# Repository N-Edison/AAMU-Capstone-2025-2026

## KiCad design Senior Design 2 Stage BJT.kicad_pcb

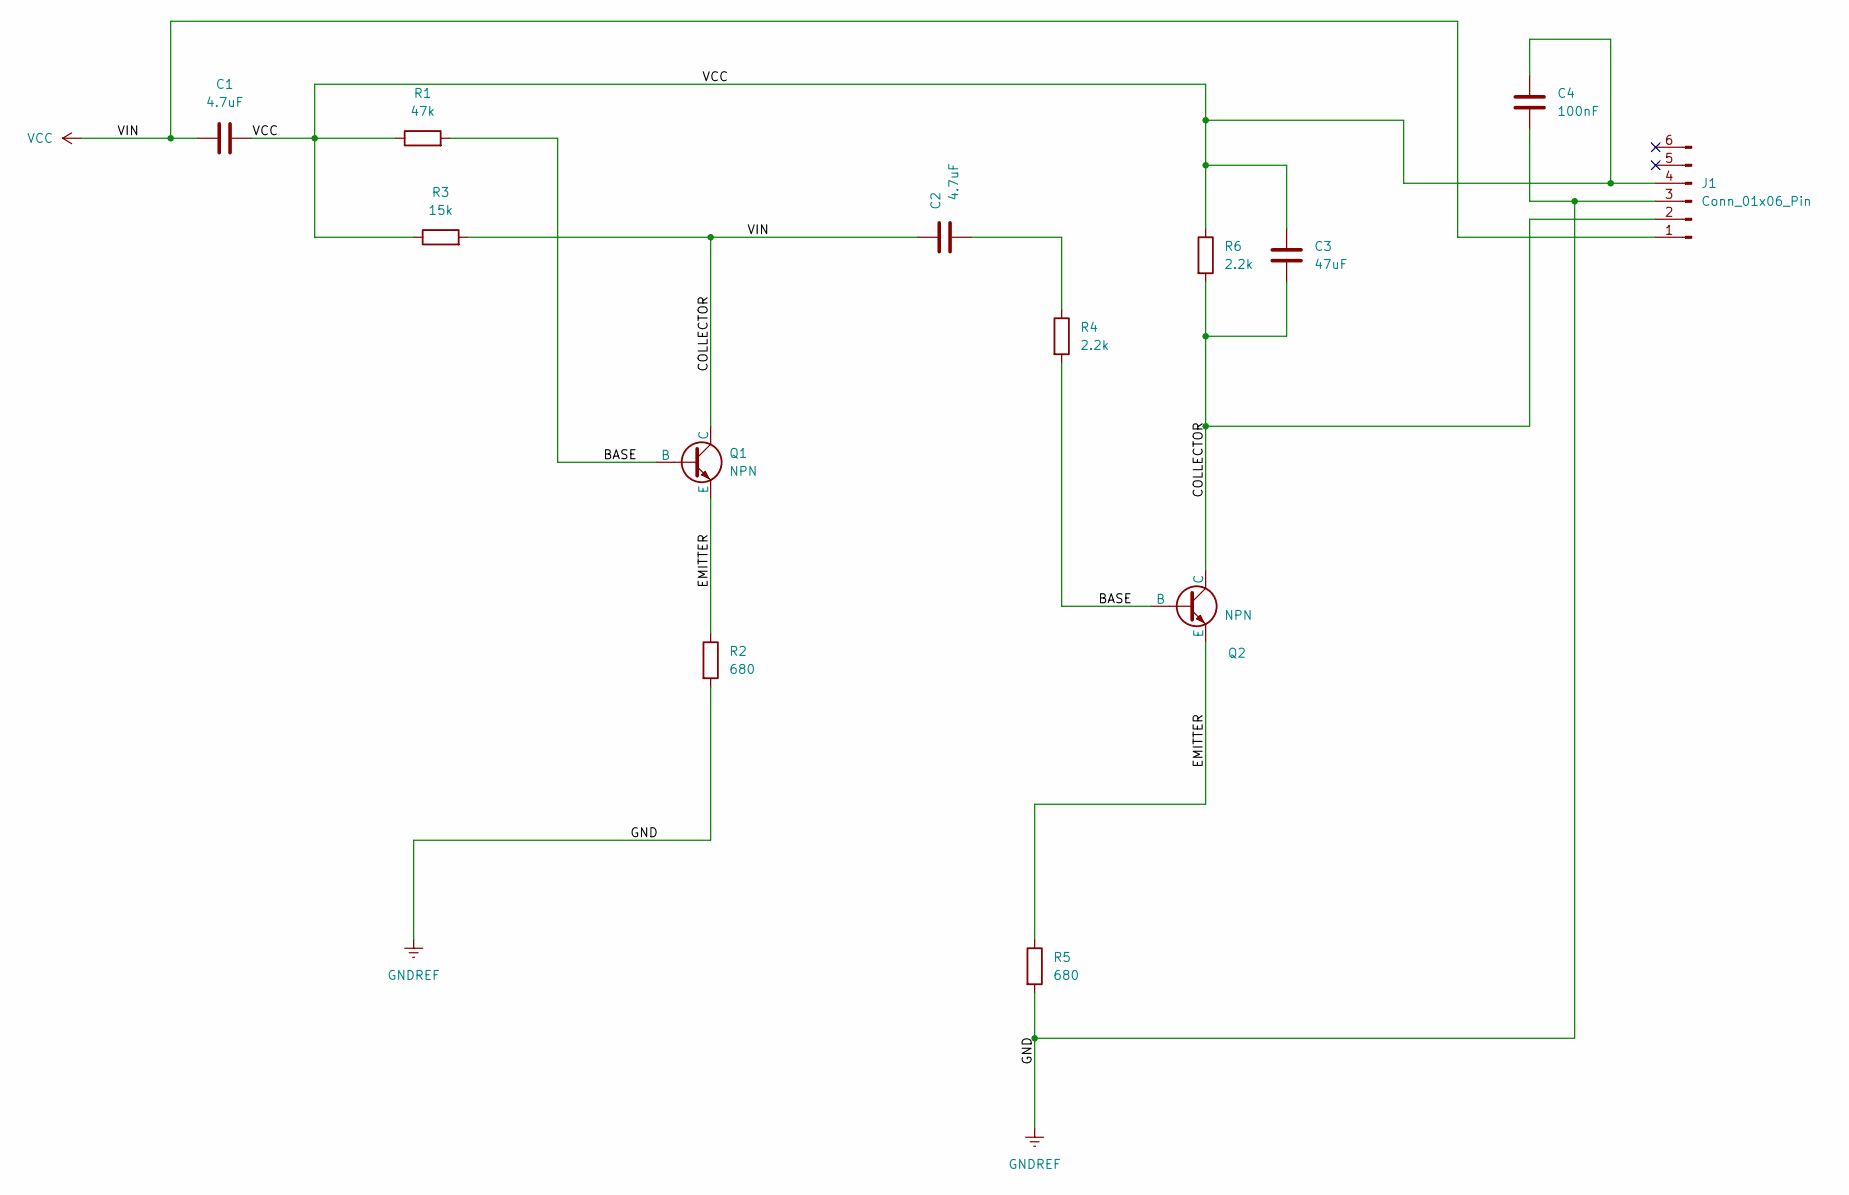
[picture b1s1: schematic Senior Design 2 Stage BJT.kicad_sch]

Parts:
C1, C2: 4.7uF; C_Disc_D5.0mm_W2.5mm_P5.00mm
C3: 47uF; C_Radial_D5.0mm_H5.0mm_P2.00mm
C4: 100nF; C_Disc_D5.0mm_W2.5mm_P5.00mm
J1: Conn_01x06_Pin; Harwin_M20-89006xx_1x06_P2.54mm_Horizontal
Q1, Q2: NPN; TO-92_Inline
R1: 47k; R_Axial_DIN0207_L6.3mm_D2.5mm_P7.62mm_Horizontal
R2, R5: 680; R_Axial_DIN0207_L6.3mm_D2.5mm_P7.62mm_Horizontal
R3: 15k; R_Axial_DIN0207_L6.3mm_D2.5mm_P7.62mm_Horizontal
R4, R6: 2.2k; R_Axial_DIN0207_L6.3mm_D2.5mm_P7.62mm_Horizontal

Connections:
/BASE: Q1.2 (B), Q2.2 (B), R1.2, R4.2
/EMITTER: Q1.3 (E), Q2.3 (E), R2.1, R5.1
GNDREF: C4.2, J1.3, R2.2, R5.2
unnamed: C2.2, R4.1
VCC: C1.1, C1.2, C2.1, C3.1, C3.2, C4.1, J1.1, J1.2, J1.4, Q1.1 (C), Q2.1 (C), R1.1, R3.1, R3.2, R6.1, R6.2

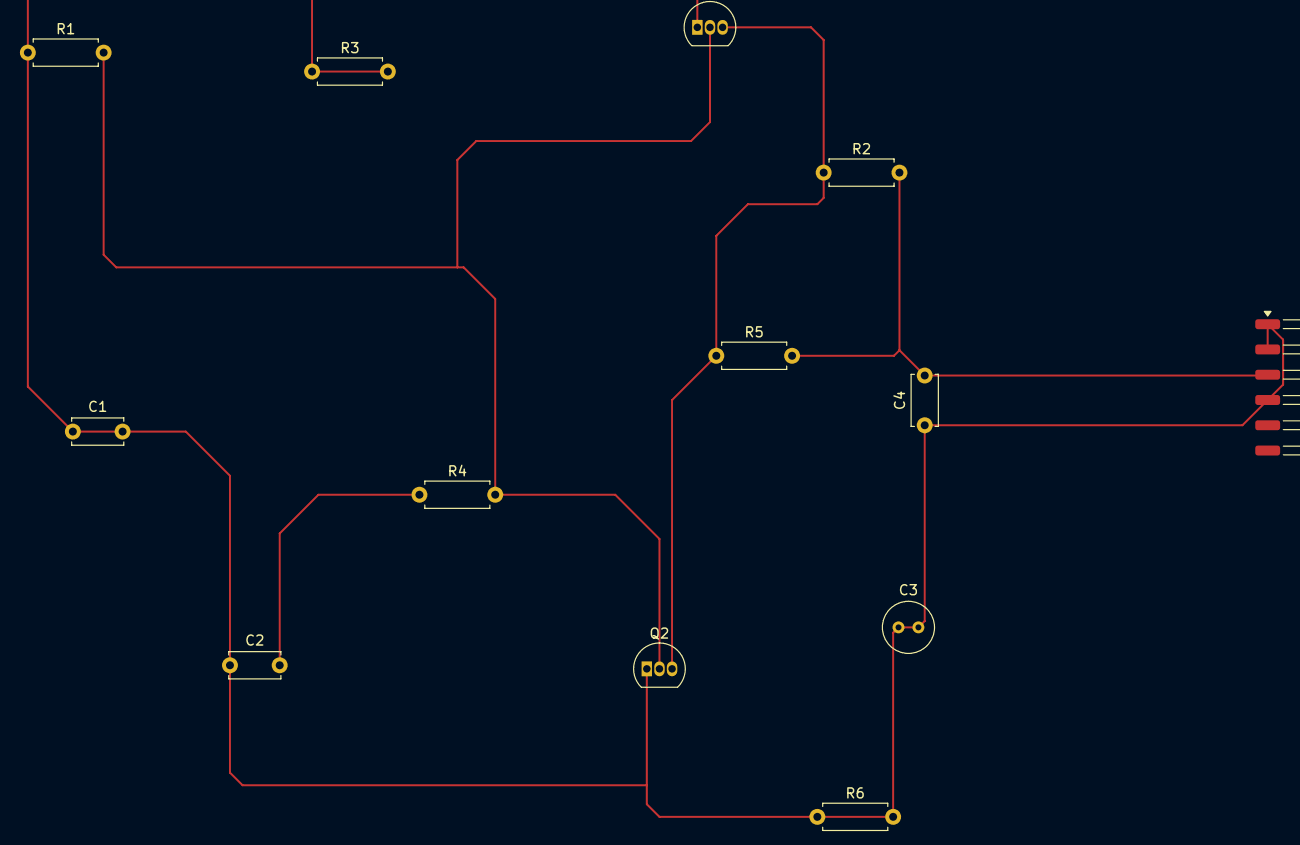
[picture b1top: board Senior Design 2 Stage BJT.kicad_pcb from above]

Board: 2 copper layers, 13 parts (0 on the bottom side), 5 nets.

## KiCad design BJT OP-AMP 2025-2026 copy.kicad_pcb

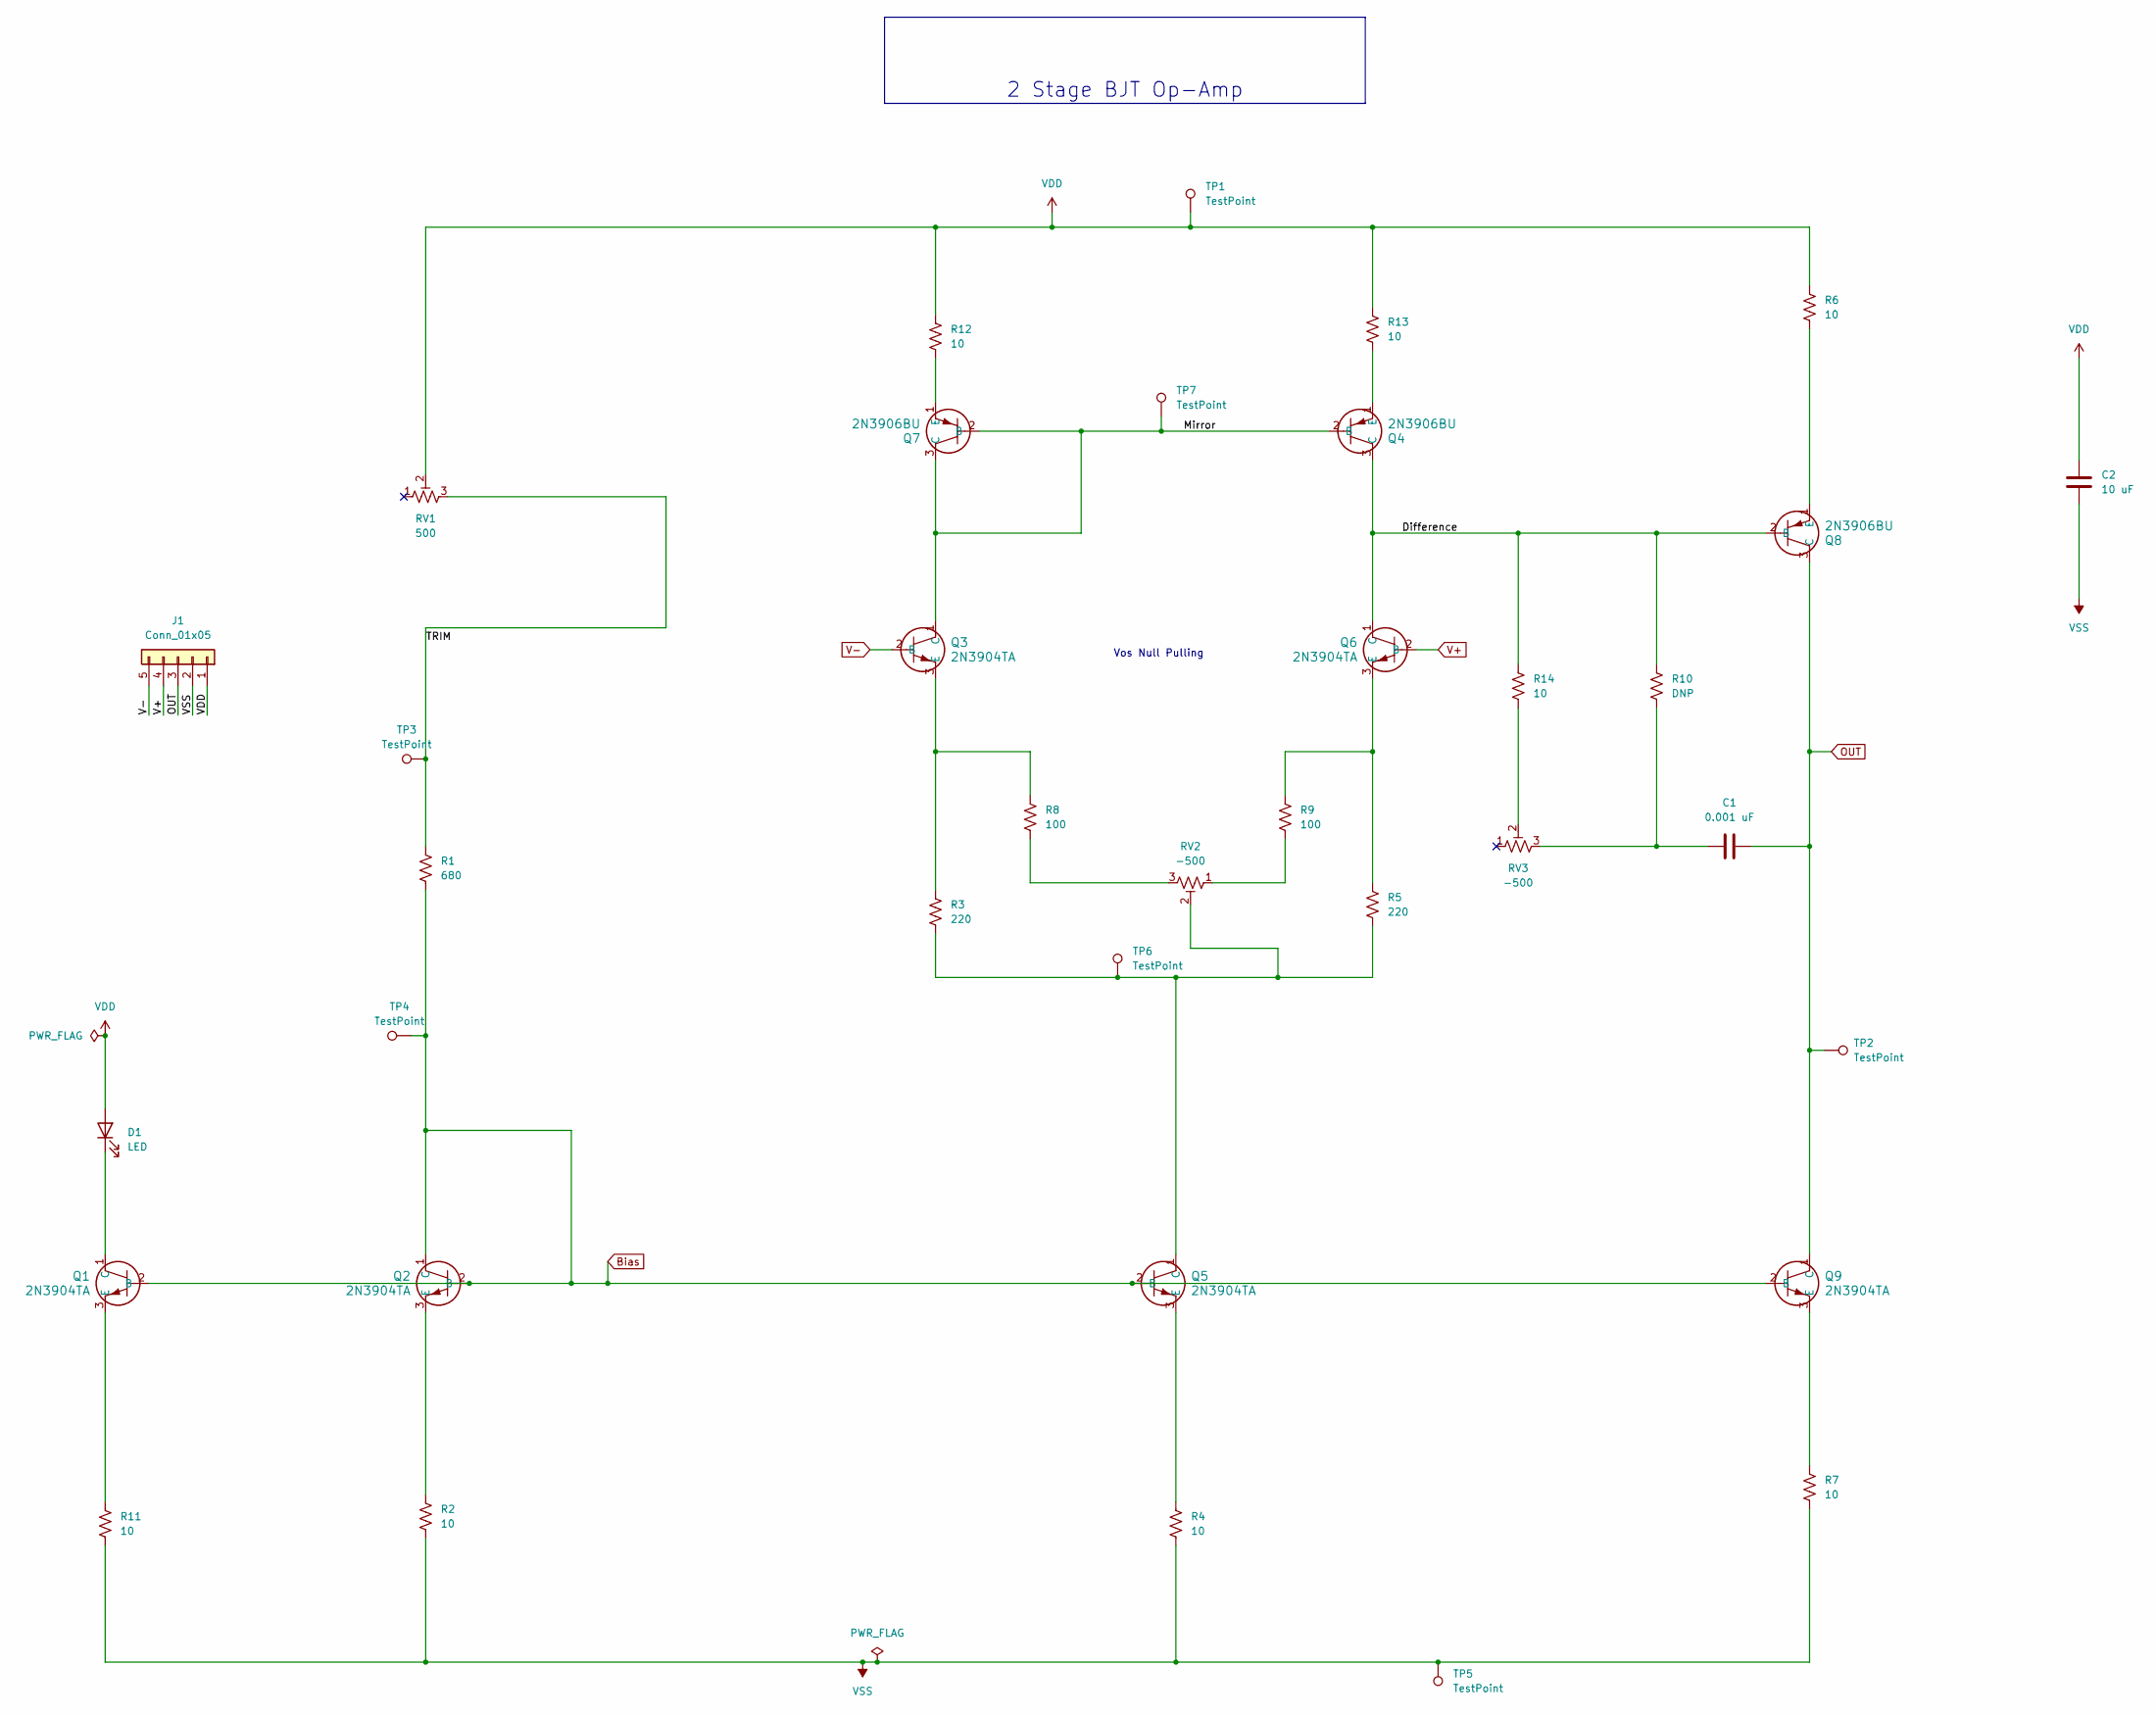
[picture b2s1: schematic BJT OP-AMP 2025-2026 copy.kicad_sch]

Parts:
C1: 0.001 uF; C_0603_1608Metric_Pad1.08x0.95mm_HandSolder
C2: 10 uF; C_0603_1608Metric_Pad1.08x0.95mm_HandSolder
D1: LED; LED_0603_1608Metric_Pad1.05x0.95mm_HandSolder
J1: Conn_01x05; PinHeader_1x05_P2.54mm_Horizontal
Q1, Q2, Q3, Q5, Q6, Q9: 2N3904TA; 2N3904TA_ONS
Q4, Q7, Q8: 2N3906BU; 2N3906BU_ONS
R1: 680; R_0603_1608Metric_Pad0.98x0.95mm_HandSolder
R2, R4, R6, R7, R11, R12, R13, R14: 10; R_0603_1608Metric_Pad0.98x0.95mm_HandSolder
R3, R5: 220; R_0603_1608Metric_Pad0.98x0.95mm_HandSolder
R8, R9: 100; R_0603_1608Metric_Pad0.98x0.95mm_HandSolder
R10: DNP; R_0603_1608Metric_Pad0.98x0.95mm_HandSolder
RV1: 500; TRIM_3306F-1-253
RV2, RV3: -500; TRIM_3306F-1-253
TP1, TP2, TP3, TP4, TP5, TP6, TP7: TestPoint; TestPoint_Pad_D2.0mm

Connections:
/Difference: Q4.3 (C), Q6.1 (C), Q8.2 (B), R10.1, R14.1
/Mirror: Q3.1 (C), Q4.2 (B), Q7.2 (B), Q7.3 (C), TP7.1
/TRIM: R1.1, RV1.3, TP3.1
Bias: Q1.2 (B), Q2.1 (C), Q2.2 (B), Q5.2 (B), Q9.2 (B), R1.2, TP4.1
unnamed: C1.1, R10.2, RV3.3
unnamed: D1.1 (K), Q1.1 (C)
unnamed: Q1.3 (E), R11.1
unnamed: Q2.3 (E), R2.1
unnamed: Q3.3 (E), R3.1, R8.1
unnamed: Q4.1 (E), R13.2
unnamed: Q5.1 (C), R3.2, R5.2, RV2.2, TP6.1
unnamed: Q5.3 (E), R4.1
unnamed: Q6.3 (E), R5.1, R9.1
unnamed: Q7.1 (E), R12.2
unnamed: Q8.1 (E), R6.2
unnamed: Q9.3 (E), R7.1
unnamed: R8.2, RV2.3
unnamed: R9.2, RV2.1
unnamed: R14.2, RV3.2
OUT: C1.2, J1.3, Q8.3 (C), Q9.1 (C), TP2.1
V+: J1.4, Q6.2 (B)
V-: J1.5, Q3.2 (B)
VDD: C2.1, D1.2 (A), J1.1, R6.1, R12.1, R13.1, RV1.2, TP1.1
VSS: C2.2, J1.2, R2.2, R4.2, R7.2, R11.2, TP5.1

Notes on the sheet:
Vos Null Pulling
2 Stage BJT Op-Amp

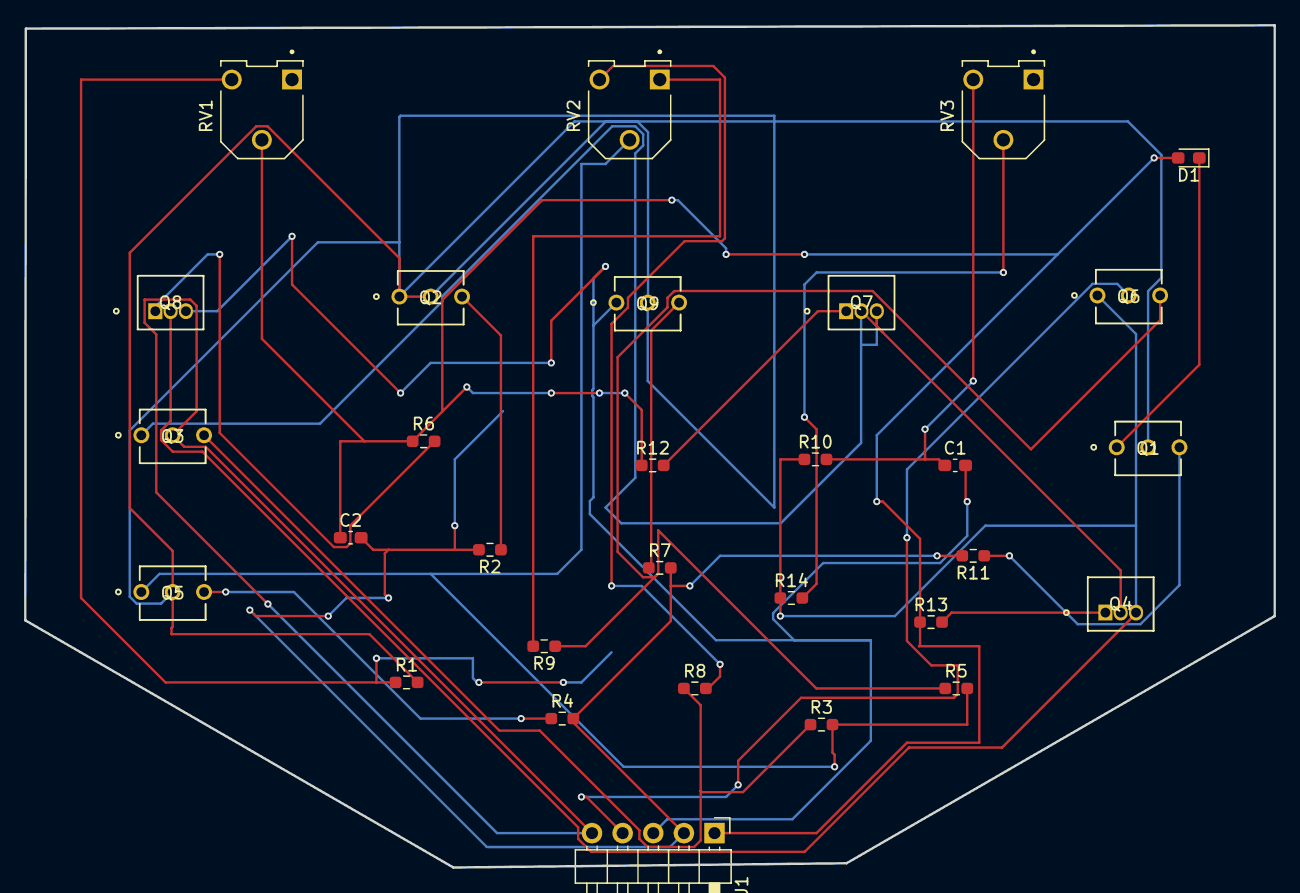
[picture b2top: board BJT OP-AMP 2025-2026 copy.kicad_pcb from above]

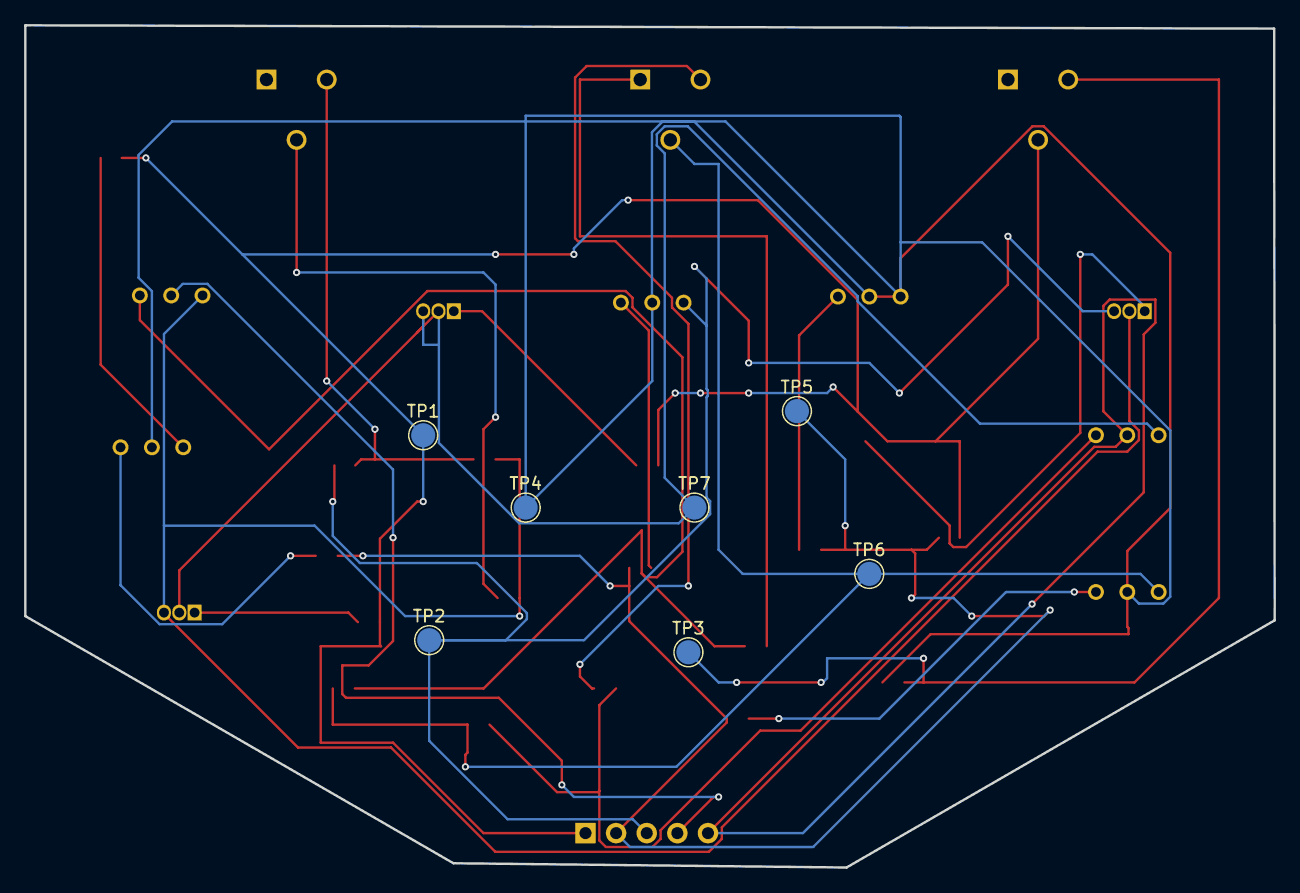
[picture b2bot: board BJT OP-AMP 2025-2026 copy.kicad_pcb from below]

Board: 2 copper layers, 103.6 x 69.9 mm, 37 parts (7 on the bottom side), 24 nets.

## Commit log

2025-09-23 BJT Op-Amp PDF & Schematics
    This is a PDF version for the BJT Op-Amp. Also, included is the BJT Schematics used with software KiCad.
2025-09-25 BJT Curve Trace Board & Plot
    This is Alabama A&M University Senior Design BJT Curve trace board schematics and plot pdf.
2025-10-04 BJT Op-Amp LTSpice Test
    This is the test data from LTSpice on the AAMU Capstone 2025-2026 BJT Op-Amp PCB that shows the board made in KiCad works.
2025-10-06 Finished Board & Updated Schematic
    This is the finished board on KiCad with downloaded footprints from Digikey for 2N3904TA & 2N3906BU. Board ran with DRC works fine but footprint clearance errors because of downloaded parts from Digi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
2025-10-06 Files Update
    Updated files so LTSpice could run correctly with BJT Op-Amp Test.
2025-10-08 Add files via upload
    Senior Design 2025-2026 Group 7
    2-Stage BJT Chip Design
2025-10-08 Schematic and PCB for 2 Stage BJT Group 7
2025-10-24 Updated BJT
    Needs an additional 3.5 mm audio jack. We can ask Dr. Eric if upgrading to an 1x8 header will suffice if we designate the audio in/outs. If not, adding a jack is pretty easy. Also, board can be route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
2025-10-24 BJT SOT Transistors Schematic and LTSpice Test
    This is the schematics of BJT Op-Amp using SOT transistors. This is a work in progress as the voltage for the output seems to be off in LTSpice with the test ran.
